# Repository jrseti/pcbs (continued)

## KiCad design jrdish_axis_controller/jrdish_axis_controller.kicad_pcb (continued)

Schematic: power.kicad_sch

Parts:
C46: 47uF; C1206; LCSC Part C403725
C47: 100nF; C0603; LCSC Part C14663
C48: 100nF; C_0402; Voltage Rated 50V; Tolerance ±10%; Part CL05B104KB54PNC; LCSC C307331
C49, C50: 10uF; C_0805; Voltage Rated 50V; Tolerance ±10%; Part GRM21BR61H106KE43L; LCSC C440198
C51: 100nF; C_0603; Voltage Rated 50V; Tolerance ±10%; Part CC0603KRX7R9BB104; LCSC C14663
C52: 22pF; C_0603; Voltage Rated 50V; Tolerance ±5%; Part CL10C220JB8NNNC; LCSC C1653
C53: 22uF; C_0805; Voltage Rated 25V; Tolerance ±20%; Part CL21A226MAQNNNE; LCSC C45783
C54: 1uF; C_0402; Voltage Rated 25V; Tolerance ±10%; Part CL05A105KA5NQNC; LCSC C52923
DC1: DC-005-2.5A-2.0; CONN-TH_DC-005-2.5A-2.0; LCSC Part C319099
F1: 1812L110/48QR; F1812; MPN 1812L110/48QR; LCSC Part C19723490
L11: 3.3uH; IND-SMD_L3.0-W3.0-1; LCSC Part C7427089
Q1, Q4: AO3407A; SOT-23-3_L2.9-W1.6-P1.90-LS2.8-BR; LCSC Part C15155
R20: 10kΩ; R_0603; Overload Voltage (Max) 75V; Tolerance ±1%; Part 0603WAF1002T5E; LCSC C22356465
R21: 976kΩ; R_0805_2012Metric; LCSC C865713
R22: 100kΩ; R_0603; Overload Voltage (Max) 75V; Tolerance ±1%; Part 0603WAF1003T5E; LCSC C25803
R23: 220kΩ; R_0603; Overload Voltage (Max) 75V; Tolerance ±1%; Part 0603WAF2203T5E; LCSC C22961
SW2: SS-12F49-G050; SW-TH_SS-12F45-GXXX; LCSC Part C2876010
TP1, TP2, TP3: RH-5016; TESTPOINT-SMD_L3.0-W2.0; MPN RH-5016; LCSC Part C5199799
U4: MP2322GQH-Z; QFN-8_L2.0-W1.5-P0.50-BL; LCSC Part C3726283

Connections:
12V: C49.1, C50.1, C51.1, Q1.3 (D), TP2.1 (1_1), U4.2 (IN), U4.3 (EN); also elsewhere on the board
/Power/12V_IN: DC1.1, F1.1, TP1.1 (1_1)
/Power/12V_IN_FUSED: C46.1, C47.1, F1.2, Q4.3 (D)
GND: C46.2, C47.2, C49.2, C50.2, C51.2, C53.2, C54.2, DC1.2, DC1.3, Q4.1 (G), R23.2, SW2.3, U4.1 (GND); also elsewhere on the board
unnamed: Q1.1 (G), SW2.2
unnamed: Q1.2 (S), Q4.2 (S), R20.1
unnamed: R20.2, SW2.1
unnamed: C48.2, U4.7 (BST)
unnamed: C52.2, R21.2, R23.1, U4.5 (FB)
unnamed: R22.1, U4.6 (PG)
unnamed: C48.1, L11.1, U4.8 (SW)
unnamed: C54.1, R22.2, U4.4 (VCC)

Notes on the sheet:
Off
12V DC input fused to 1.1A max
12V to 3V3 Buck
Q4 protects against reverse polarity. SW2 controls the gate of Q1, turning current on/off. The MOSFET is P-Channel.
12V_IN_FUSED is the input, 12V is the output (load)
Notes:
gate
0.1%
1.1A Fuse 48VDC
50V
From MP2322 Datasheet:
Reverse Voltage Protection P-Channel MOSFET
25V
Circuit to convert 12V DC to 3V3 DC 12V is reverse polatiry and over voltage protected MP2322 used to convert 12V to 3V3 DC 12V DC out will draw max 600mA 3V3 DC out will draw max 400mA Buck modeled after John Teel's YouTube video: https://www.youtube.com/watch?v=rLHW4gU6idU and referencing the MP2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
Power Flags

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
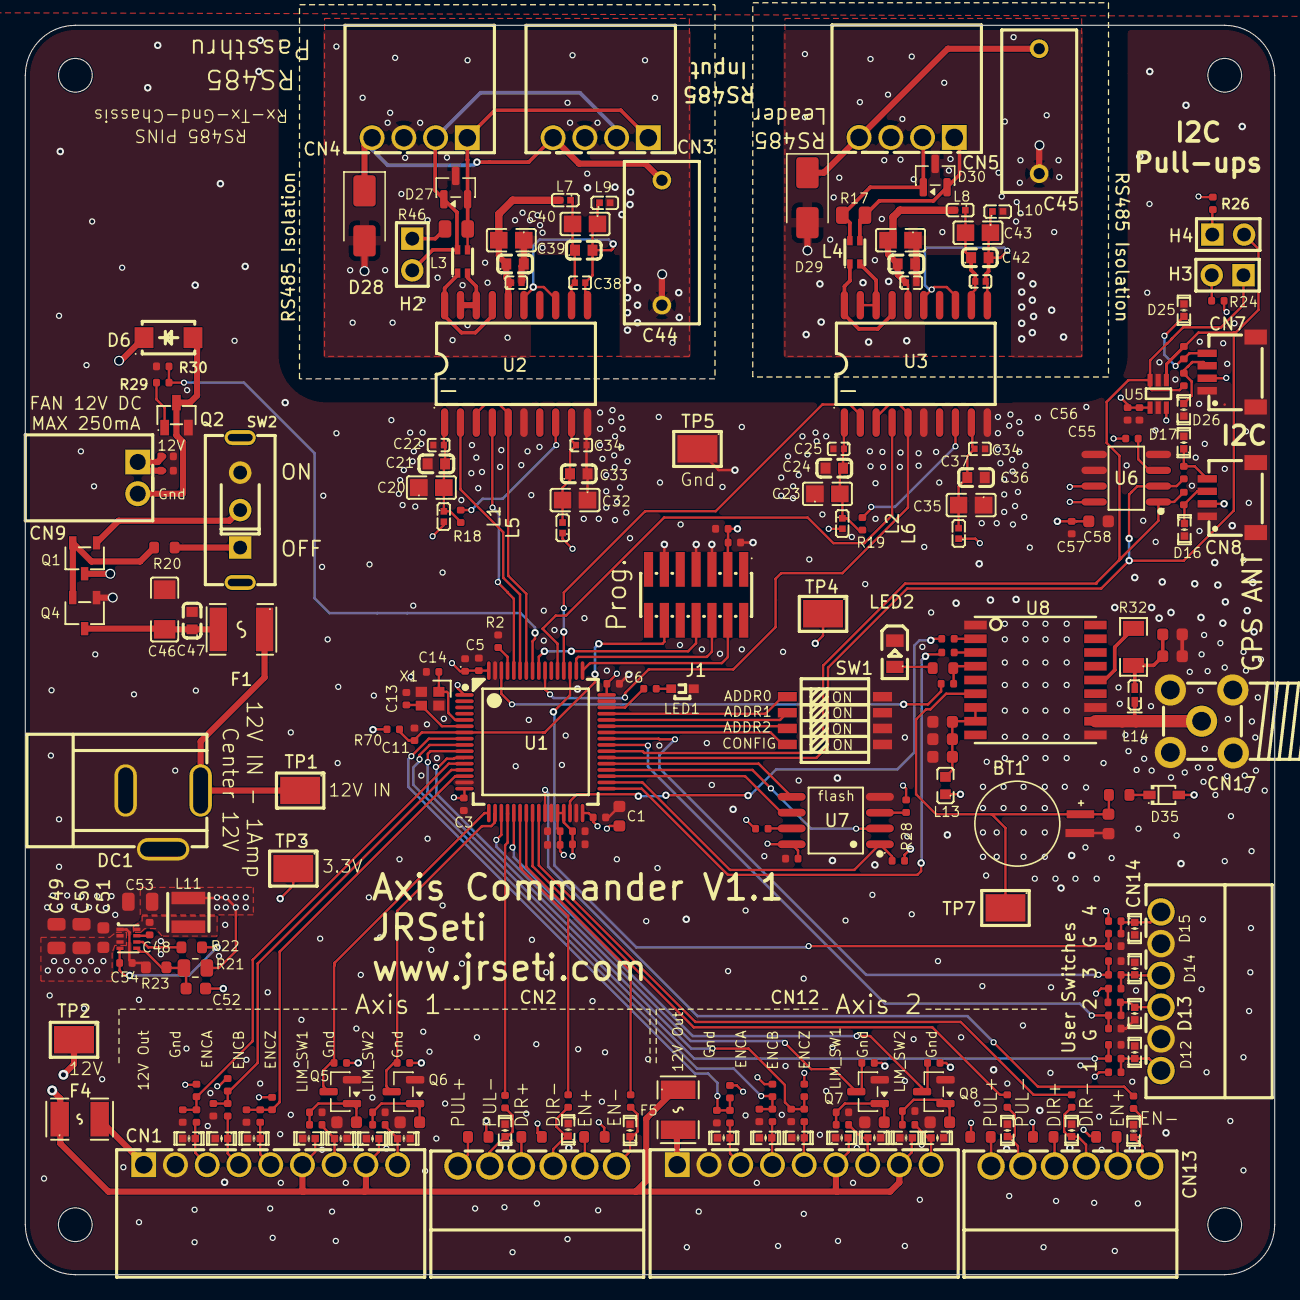
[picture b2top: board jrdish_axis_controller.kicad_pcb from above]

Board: 4 copper layers, 100.0 x 100.0 mm, 248 parts (0 on the bottom side), 140 nets.

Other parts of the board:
C12#2: 10nF; C_0603
M1, M1#2, M1#3, M1#4: MountingHole_2.7mm_M2.5_ISO14580

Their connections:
GND: C12#2.2; also elsewhere on the board

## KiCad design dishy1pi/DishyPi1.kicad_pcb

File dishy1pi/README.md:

# Dishy1Pi Hardware

The hardware part of the Dishy1Pi project is a Raspberry Pi Hat board which interfaces the Raspberry Pi GPIO pins with the satellite dish motor controllers, encoders, and various sensors. An important aspect of this board is that the Raspberry Pi is optically isolated from the hardware connected to the satellite dish.

Although this project is tailored to controlling a satellite dish, it can also be used for controlling other motor control systems that require isolation and encoder feedback.

## Parts Library

The PCB will be assembled by JCLPCB. The project will require parts number identification to be compatible with LCSC part numbers. See [Library README](libs/README.md)

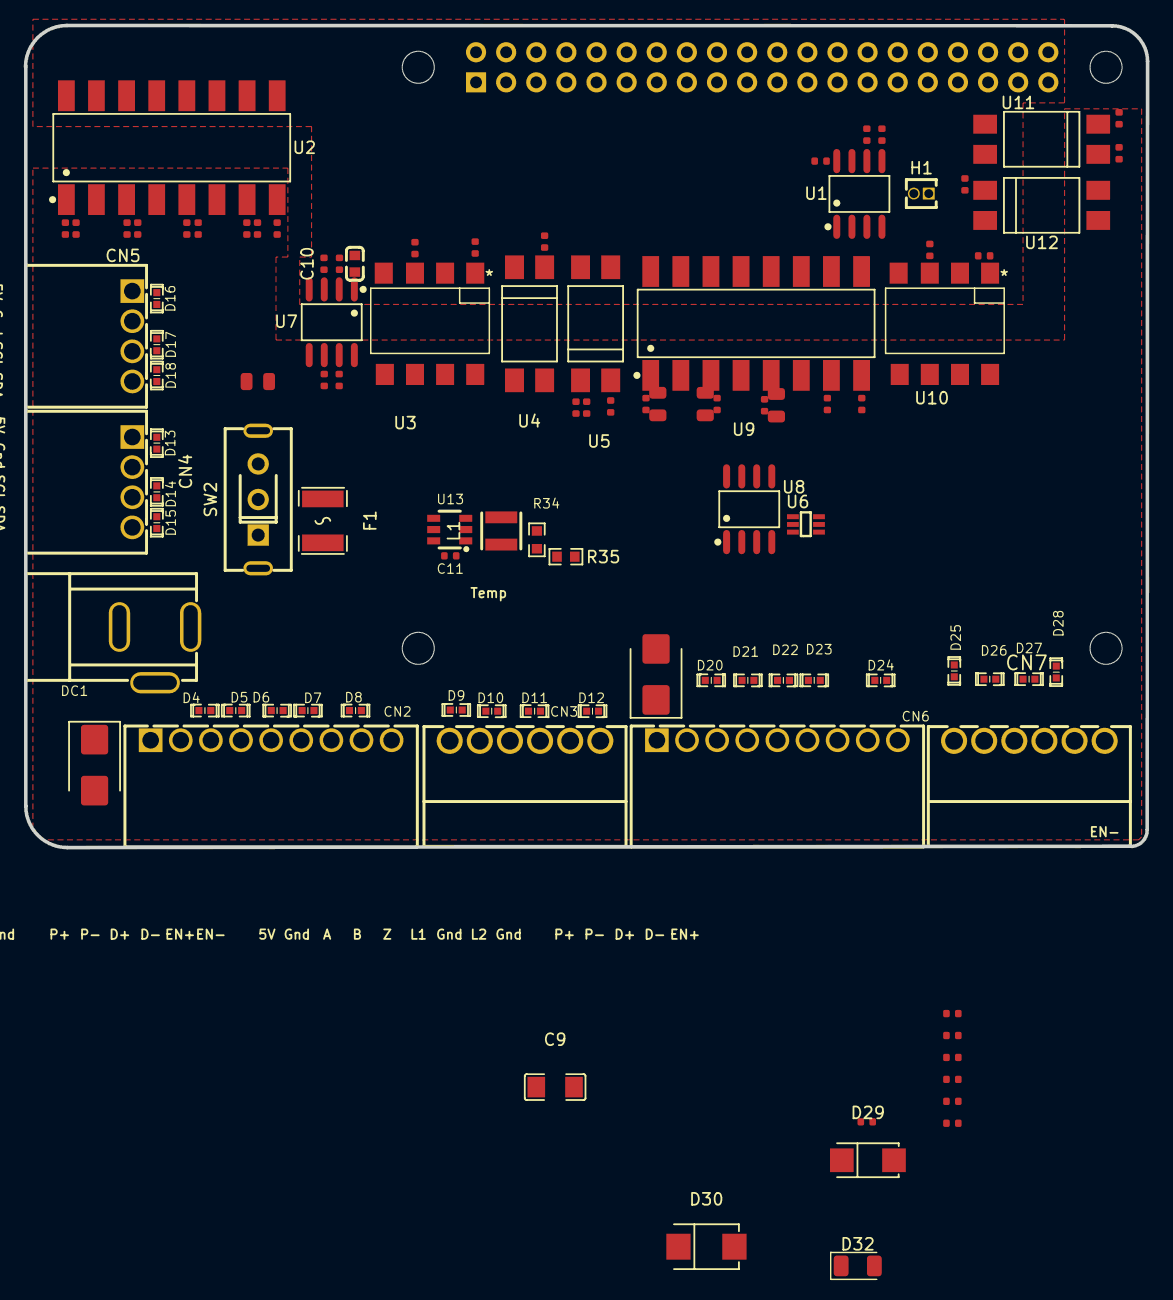
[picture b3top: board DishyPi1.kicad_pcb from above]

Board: 4 copper layers, 94.6 x 69.3 mm, 106 parts (1 on the bottom side), 67 nets, no tracks yet.

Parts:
C3, C5, C6, C7, C8, C11: 100nF; C_0402
C4: 100pF; C_0402
C9: 47uF; C1206
C10: 100nF; C0603
C12, C13, C14: 10uF; C_0805
C15: 100nF; C_0805
CN2, CN6: KF2EDGR-2.54-9P; CONN-TH_9P-P2.54_KF2EDGR-2.54-9P
CN3, CN7: KF2EDGR-2.54-6P; CONN-TH_KF2EDGR-2.54-6P
CN4, CN5: KF2EDGR-2.54-4P; CONN-TH_4P-P2.54_KF2EDGR-2.54-4P
D4, D5, D6, D7, D8, D9, D10, D11, D12, D13, D14, D15, D16, D17, D18, D20, D21, D22, D23, D24, D25, D26, D27, D28: TPESD0402G05V; D0402-BI
D29: SS34; SMA_L4.3-W2.6-LS5.2-RD
D30: SMBJ18A_C78412; SMB_L4.6-W3.6-LS5.3-RD
D32: LED; LED_1206_3216Metric
D33, D34: SMBJ16A; D_SMB
DC1: DC-005-2.5A-2.0; CONN-TH_DC-005-2.5A-2.0
F1: 1812L110/33MR; F1812
H1: 1.27MM/1*2P; HDR-TH_2P-P1.27-V-M
J1: Conn_02x20_Odd_Even; PinSocket_2x20_P2.54mm_Vertical
L1: 4.7uH; IND-SMD_L3.0-W3.0-1
MH1, MH2, MH3, MH4: MountingHole_2.7mm_M2.5
R2, R3: 3.9kΩ; R_0402
R4, R6, R8, R12, R13, R14, R21, R23, R25, R29, R30, R31: 1kΩ; R_0402
R5, R7, R9, R22, R24, R26: 10kΩ; R_0402
R10, R27: 220Ω; R_0402
R11, R16, R28, R33: 22kΩ; R_0402
R15, R32: 470Ω; R_0402
R17, R18, R19, R20: 4.7kΩ; R_0402
R34: 54.9k; R0603
R35: 10k; R0603
R36: 2.2kΩ; R_0402
SW2: SS-12F49-G050; SW-TH_SS-12F45-GXXX
U1: CAT24C256WI-GT3; SOIC-8_L4.9-W3.9-P1.27-LS6.0-BL
U2, U9: LTV-847S; SMD-16_L20.0-W6.5-P2.54-LS10.2-BL
U3, U10: LTV-827S-TA1; LTV827S-TA1
U4, U5, U11, U12: LTV-817S-TA1; LTV817S
U6: LTC4311ISC6#TRPBF; SC-70-6_L2.2-W1.3-P0.65-LS2.2-BL
U7: ISO1540DR; SOIC-8_L4.9-W3.9-P1.27-LS6.0-BL
U8: LM75BIMX-5/NOPB; SOIC-8_L4.9-W3.9-P1.27-LS6.0-BL
U13: TPS561201DDCR; SOT-23-6_L2.9-W1.6-P0.95-LS2.8-BR

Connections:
12V_PROT: C9.1, C10.1, C14.1, C15.1, CN2.1, CN6.1, D29.1 (K), D30.1 (K), D33.1, D34.1, U13.3 (VIN), U13.5 (EN)
+3.3V: C3.1, C6.1, H1.1, J1.1, J1.17, R2.1, R3.1, R17.1, R18.1, U1.8 (VCC), U7.1 (VCC1)
+5V: C5.1, C7.1, C8.1, C12.1, C13.1, CN3.1, CN3.3, CN3.5, CN4.1, CN5.1, CN7.1, CN7.3, CN7.5, D9.1 (K), D13.1 (K), D16.2 (A), D25.1 (K), D32.2 (A), L1.2, R4.1, R5.1, R6.1, R7.1, R8.1, R9.1, R10.1, R15.1, R16.2, R19.1, R20.1, R21.1, R22.1, R23.1, R24.1, R25.1, R26.1, R27.1, R28.2, R32.1, R33.2, R34.2, U6.1 (VCC), U6.3 (ENABLE), U7.8 (VCC2), U8.7 (A0), U8.8 (+VS)
/12v_in/12V_IN: DC1.1, SW2.1
/12v_in/VBST-SW-L1: C11.2, L1.1, U13.2 (SW)
/I2C/SCL: CN4.3, CN5.3, D14.1 (K), D17.2 (A), R20.2, U6.4 (BUS2), U7.6 (SCL2), U8.2 (SCL)
/I2C/SDA: CN4.4, CN5.4, D15.1 (K), D18.2 (A), R19.2, U6.6 (BUS1), U7.7 (SDA2), U8.1 (SDA)
/ID_SCL: J1.28, R2.2, U1.6 (SCL)
/ID_SDA: J1.27, R3.2, U1.5 (SDA)
/IO/DIR-: CN3.4, D11.1 (K), U3.8
/IO/ENC_A: CN2.3, D4.1 (K), R9.2, U2.2 (CAT1)
/IO/ENC_B: CN2.4, D5.1 (K), R7.2, U2.4 (CAT2)
/IO/ENC_Z: CN2.5, D6.1 (K), R5.2, U2.6 (CAT3)
/IO/LIM_1: CN2.6, D7.1 (K), R11.1, U2.8 (CAT4)
/IO/LIM_2: CN2.8, D8.1 (K), R16.1, U5.2
/IO/MF-: CN3.6, D12.1 (K), U4.4
/IO/PUL-: CN3.2, D10.1 (K), U3.6
/io2/DIR-: CN7.4, D27.1 (K), U10.6
/io2/ENC_A: CN6.3, D20.1 (K), R26.2, U9.2 (CAT1)
/io2/ENC_B: CN6.4, D21.1 (K), R24.2, U9.4 (CAT2)
/io2/ENC_Z: CN6.5, D22.1 (K), R22.2, U9.6 (CAT3)
/io2/LIM_1: CN6.6, D23.1 (K), R28.1, U9.8 (CAT4)
/io2/LIM_2: CN6.8, D24.1 (K), R33.1, U12.2
/io2/MF-: CN7.6, D28.1 (K), U11.4
/io2/PUL-: CN7.2, D26.1 (K), U10.8
A_DIR/19: J1.35, R30.1
A_ENC_A/5: J1.29, U9.16 (COL1)
A_ENC_B/6: J1.31, U9.14 (COL2)
A_ENC_Z/26: J1.37, U9.12 (COL3)
A_LIM_1/12: J1.32, U9.10 (COL4)
A_LIM_2/21: J1.40, U12.4
A_MF/20: J1.38, R31.1
A_PUL/13: J1.33, R29.1
E_DIR/23: J1.16, R12.1
E_ENC_A/17: J1.11, U2.16 (COL1)
E_ENC_B/22: J1.13, U2.14 (COL2)
E_ENC_Z/27: J1.15, U2.12 (COL3)
E_LIM_1/25: J1.22, U2.10 (COL4)
E_LIM_2/16: J1.36, U5.4
E_MF/24: J1.18, R14.1
E_PUL/18: J1.12, R13.1
GNDIO: C4.2, C5.2, C7.2, C8.2, C9.2, C10.2, C12.2, C13.2, C14.2, C15.2, CN2.2, CN2.7, CN2.9, CN4.2, CN5.2, CN6.2, CN6.7, CN6.9, D4.2 (A), D5.2 (A), D6.2 (A), D7.2 (A), D8.2 (A), D9.2 (A), D10.2 (A), D11.2 (A), D12.2 (A), D13.2 (A), D14.2 (A), D15.2 (A), D16.1 (K), D17.1 (K), D18.1 (K), D20.2 (A), D21.2 (A), D22.2 (A), D23.2 (A), D24.2 (A), D25.2 (A), D26.2 (A), D27.2 (A), D28.2 (A), D30.2 (A), D33.2, D34.2, DC1.2, DC1.3, R11.2, R35.2, R36.2, U3.5, U3.7, U4.3, U6.2 (GND), U6.5 (GND), U7.5 (GND2), U8.4 (GND), U8.5 (A2), U8.6 (A1), U10.5, U10.7, U11.3, U13.1 (GND)
GNDPI: C3.2, C6.2, J1.6, J1.9, J1.14, J1.20, J1.25, J1.30, J1.34, J1.39, U1.1 (A0), U1.2 (A1), U1.3 (A2), U1.4 (VSS), U2.9 (EM4), U2.11 (EM3), U2.13 (EM2), U2.15 (EM1), U3.2, U3.4, U4.2, U5.3, U7.4 (GND1), U9.9 (EM4), U9.11 (EM3), U9.13 (EM2), U9.15 (EM1), U10.2, U10.4, U11.2, U12.3
unnamed: D29.2 (A), F1.2
unnamed: D32.1 (K), R36.1
unnamed: F1.1, SW2.2
unnamed: R12.2, U3.1
unnamed: R13.2, U3.3
unnamed: R14.2, U4.1
unnamed: R15.2, U5.1
unnamed: R29.2, U10.1
unnamed: R30.2, U10.3
unnamed: R31.2, U11.1
unnamed: R32.2, U12.1
unnamed: H1.2, U1.7 (WP)
unnamed: R8.2, U2.1 (AN1)
unnamed: R6.2, U2.3 (AN2)
unnamed: R4.2, U2.5 (AN3)
unnamed: C4.1, R10.2, U2.7 (AN4)
unnamed: R25.2, U9.1 (AN1)
unnamed: R23.2, U9.3 (AN2)
unnamed: R21.2, U9.5 (AN3)
unnamed: R27.2, U9.7 (AN4)
unnamed: C11.1, U13.6 (VBST)
unnamed: R34.1, R35.1, U13.4 (VFB)
PI_SCL: J1.5, R17.2, U7.3 (SCL1)
PI_SDA: J1.3, R18.2, U7.2 (SDA1)

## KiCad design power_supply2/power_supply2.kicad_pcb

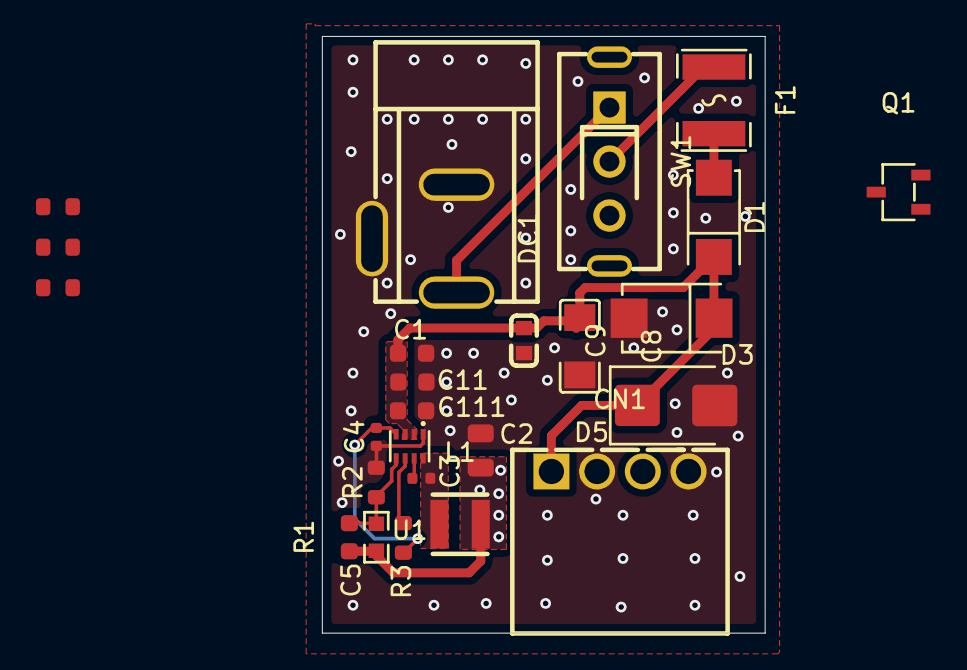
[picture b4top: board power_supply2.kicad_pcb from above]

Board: 4 copper layers, 24.6 x 33.1 mm, 25 parts (0 on the bottom side), 13 nets.

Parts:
C1: 100nF; C_0603
C2: 22uF; C_0805
C3: 22pF; C_0402
C4: 1uF; C_0402
C5: 22pF; C_0603
C8: 47uF; C1206
C9: 100nF; C0603
C11, C111: 10uF; C_0603
CN1: KF2EDGR-2.54-4P; CONN-TH_4P-P2.54_KF2EDGR-2.54-4P
D1: SS34; SMA_L4.3-W2.6-LS5.2-RD
D3: SMBJ18A; SMB_L4.6-W3.6-LS5.3-RD
D5: SMBJ16A; D_SMB
DC1: DC-005-2.5A-2.0; CONN-TH_DC-005-2.5A-2.0
F1: 1812L110/33MR; F1812
L1: 4.7uH; IND-SMD_L3.0-W3.0-1
Q1: AO3407A; SOT-23-3_L2.9-W1.6-P1.90-LS2.8-BR
R1: 1621Ω; R0603
R2: 220kΩ; R_0603
R2#2: 220Ω; R_0603
R3: 200kΩ; R_0603
R3#2: 100kΩ; R_0603
R4: 10kΩ; R_0603
SW1: SS-12F49-G050; SW-TH_SS-12F45-GXXX
U1: MP2322GQH-Z; QFN-8_L2.0-W1.5-P0.50-BL

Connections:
/5V_OUT: C2.1, C5.1, CN1.3, L1.2, R1.1
/12V_IN: DC1.1, F1.1
/12V_IN_FUSED: C8.1, C9.1, F1.2, Q1.3 (D), R4.1
/12V_OUT: C1.1, C11.1, C111.1, CN1.1, Q1.2 (S), U1.2 (IN), U1.3 (EN)
/12V_PROT: D1.1 (K), D3.1 (K), D5.1
GND: C1.2, C2.2, C4.2, C8.2, C9.2, C11.2, C111.2, CN1.2, CN1.4, D3.2 (A), D5.2, DC1.2, DC1.3, R2.2, R2#2.2, SW1.3, U1.1 (GND)
unnamed: Q1.1 (G), SW1.2
unnamed: R4.2, SW1.1
unnamed: C3.1, U1.7 (BST)
unnamed: C5.2, R1.2, R2.1, R2#2.1, U1.5 (FB)
unnamed: R3.1, R3#2.1, U1.6 (PG)
unnamed: C3.2, L1.1, U1.8 (SW)
unnamed: C4.1, R3.2, R3#2.2, U1.4 (VCC)

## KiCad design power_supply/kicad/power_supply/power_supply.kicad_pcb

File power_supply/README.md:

# Power Supply

This is a simple PCB to test creating several voltages that are used on the Dishy1Pi PCB. Once this cirction is tested as working, the relevant schematic parts will be moved over to the DishyPi1 schematic. The voltages needed are:
- 12V to power each of the 2 encoders. This voltage is supplied from an external power supply and protected by a PTC fuse on the Dishy1Pi PCB. Also reverse polatiry protected.
- 5V to power the logic circuity on the Dishy1Pi PCB. This voltage is generated on this power supply PCB from the 12-24V input voltage using a buck converter.

I need to learn how to design a power supply for a PCB board and get some experience with power supply design.

Project Goals:
- Design a power supply PCB that can take an input voltage range of 12-24VDC
- Output a stable 5VDC at up to 1A
Output clean 12V for each of the 2 encoders
- Create a schematic and PCB layout for the power supply that can be manufactured by JLCPCB.
- Get a board manufactureed and assembled by JLCPCB and test it, verify it works.
- Move the design of the power circuit to the dishy1pi project.

KiCad will be used for this project.

Used TI's WEBENCH Power Designer to design the power supply around the TPS561201DDCR buck converter IC. Link: https://webench.ti.com/power-designer/

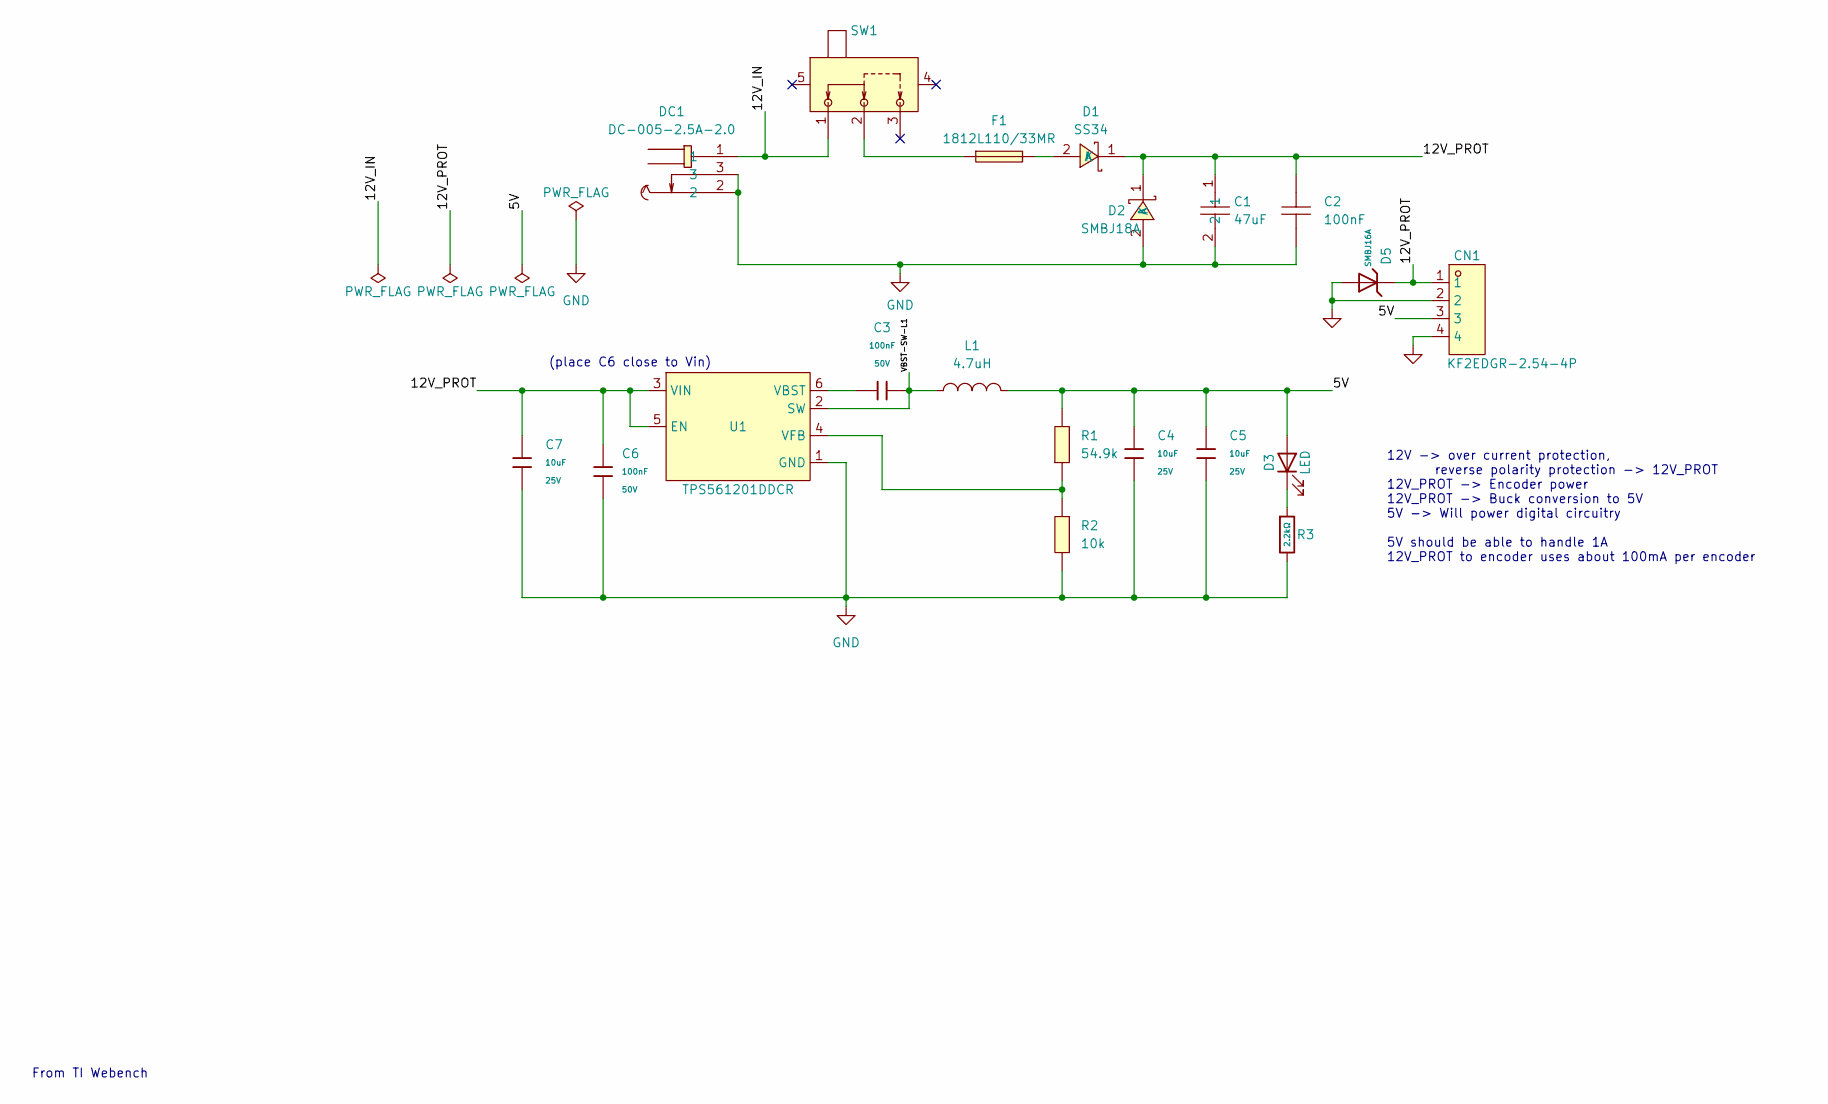
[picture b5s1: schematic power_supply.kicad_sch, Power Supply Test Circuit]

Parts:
C1: 47uF; C1206; LCSC Part C403725
C2: 100nF; C0603; LCSC Part C14663
C3: 100nF; C_0402; Voltage Rated 50V; Tolerance ±10%; Part CL05B104KB54PNC; LCSC C307331
C4, C5, C7: 10uF; C_0805; Voltage Rated 25V; Tolerance ±10%; Part CL21A106KAYNNNE; LCSC C15850
C6: 100nF; C_0805; Voltage Rated 50V; Tolerance ±10%; Part CC0805KRX7R9BB104; LCSC C49678
CN1: KF2EDGR-2.54-4P; CONN-TH_4P-P2.54_KF2EDGR-2.54-4P; LCSC Part C577596
D1: SS34; SMA_L4.3-W2.6-LS5.2-RD; LCSC Part C8678
D2: SMBJ18A; SMB_L4.6-W3.6-LS5.3-RD; LCSC Part C2965323
D3: LED; LED_1206_3216Metric; LCSC Part C5264252
D5: SMBJ16A; D_SMB; Part SMBJ16A; LCSC C19077571
DC1: DC-005-2.5A-2.0; CONN-TH_DC-005-2.5A-2.0; LCSC Part C319099
F1: 1812L110/33MR; F1812; LCSC Part C142747
L1: 4.7uH; IND-SMD_L3.0-W3.0-1; LCSC Part C7427089
R1: 54.9k; R0603; LCSC Part C23077
R2: 10k; R0603; LCSC Part C25804
R3: 2.2kΩ; R_0402; Overload Voltage (Max) 50V; Tolerance ±1%; Part 0402WGF2201TCE; LCSC C25879
SW1: SS-12F49-G050; SW-TH_SS-12F45-GXXX; LCSC Part C2876010
U1: TPS561201DDCR; SOT-23-6_L2.9-W1.6-P0.95-LS2.8-BR; LCSC Part C220433

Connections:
/5V: C4.1, C5.1, CN1.3, D3.2 (A), L1.2, R1.2
/12V_IN: DC1.1, SW1.1
/12V_PROT: C1.1, C2.1, C6.1, C7.1, CN1.1, D1.1 (K), D2.1 (K), D5.1, U1.3 (VIN), U1.5 (EN)
/VBST-SW-L1: C3.2, L1.1, U1.2 (SW)
GND: C1.2, C2.2, C4.2, C5.2, C6.2, C7.2, CN1.2, CN1.4, D2.2 (A), D5.2, DC1.2, DC1.3, R2.2, R3.2, U1.1 (GND)
unnamed: D1.2 (A), F1.2
unnamed: D3.1 (K), R3.1
unnamed: F1.1, SW1.2
unnamed: C3.1, U1.6 (VBST)
unnamed: R1.1, R2.1, U1.4 (VFB)

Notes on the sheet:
From TI Webench
(place C6 close to Vin)
12V -> over current protection, reverse polarity protection -> 12V_PROT 12V_PROT -> Encoder power 12V_PROT -> Buck conversion to 5V 5V -> Will power digital circuitry 5V should be able to handle 1A 12V_PROT to encoder uses about 100mA per encoder

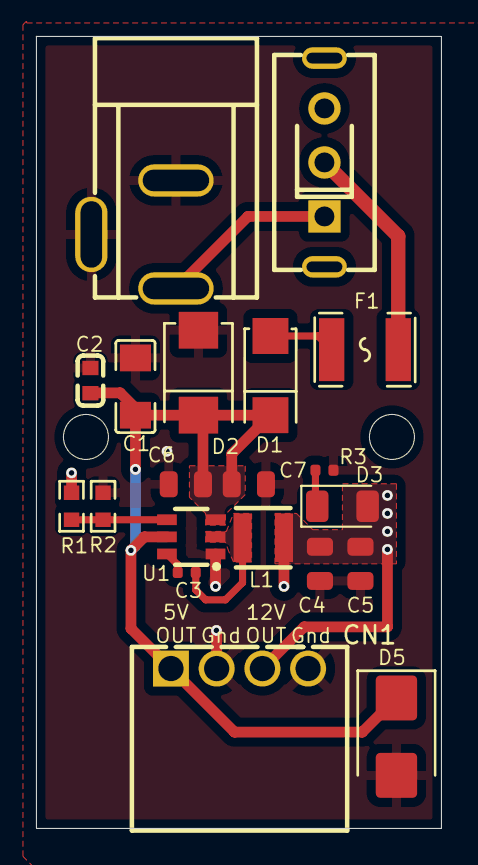
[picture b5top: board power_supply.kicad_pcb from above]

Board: 4 copper layers, 22.5 x 44.0 mm, 20 parts (0 on the bottom side), 10 nets.

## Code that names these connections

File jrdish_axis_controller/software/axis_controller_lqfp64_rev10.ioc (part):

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Mcu.Name=STM32G474R(B-C-E)Tx
Mcu.Package=LQFP64
Mcu.UserName=STM32G474RETx
PA0.GPIOParameters=GPIO_Label
PA0.GPIO_Label=ENC1_A
PA0.Signal=S_TIM2_CH1
PA1.GPIOParameters=GPIO_Label
PA1.GPIO_Label=ENC1_B
PA1.Signal=S_TIM2_CH2
PA10.GPIOParameters=GPIO_PuPd,GPIO_Label
PA10.GPIO_Label=ADDR1
PA10.GPIO_PuPd=GPIO_PULLUP
PA10.Signal=GPIO_Input
PA11.GPIOParameters=GPIO_PuPd,GPIO_Label
PA11.GPIO_Label=ADDR0
PA11.GPIO_PuPd=GPIO_PULLUP
PA11.Signal=GPIO_Input
PA12.GPIOParameters=GPIO_Label
PA12.GPIO_Label=STATUS_LED
PA12.Signal=GPIO_Output
PA13.Mode=Trace_Asynchronous_SW
PA13.Signal=SYS_JTMS-SWDIO
PA14.Mode=Trace_Asynchronous_SW
PA14.Signal=SYS_JTCK-SWCLK
PA15.GPIOParameters=GPIO_PuPd,GPIO_Label
PA15.GPIO_Label=USER_SW_4
PA15.GPIO_PuPd=GPIO_PULLUP
PA15.Signal=GPIO_Input
PA2.GPIOParameters=GPIO_PuPd,GPIO_Label
PA2.GPIO_Label=ENC1_Z
PA2.GPIO_PuPd=GPIO_PULLUP
PA2.Signal=GPXTI2
PA3.GPIOParameters=GPIO_PuPd,GPIO_Label
PA3.GPIO_Label=LIMIT1_SW1
PA3.GPIO_PuPd=GPIO_PULLUP
PA3.Signal=GPIO_Input
PA4.GPIOParameters=GPIO_PuPd,GPIO_Label
PA4.GPIO_Label=LIMIT1_SW2
PA4.GPIO_PuPd=GPIO_PULLUP
PA4.Signal=GPIO_Input
PA5.GPIOParameters=GPIO_PuPd,GPIO_Label
PA5.GPIO_Label=LIMIT2_SW1
PA5.GPIO_PuPd=GPIO_PULLUP
PA5.Signal=GPIO_Input
PA6.GPIOParameters=GPIO_Label
PA6.GPIO_Label=PUL1
PA6.Signal=S_TIM16_CH1
PA7.GPIOParameters=GPIO_PuPd,GPIO_Label
PA7.GPIO_Label=LIMIT2_SW2
PA7.GPIO_PuPd=GPIO_PULLUP
PA7.Signal=GPIO_Input
PA8.GPIOParameters=GPIO_PuPd,GPIO_Label
PA8.GPIO_Label=CONFIG_SW
PA8.GPIO_PuPd=GPIO_PULLUP
PA8.Signal=GPIO_Input
PA9.GPIOParameters=GPIO_PuPd,GPIO_Label
PA9.GPIO_Label=ADDR2
PA9.GPIO_PuPd=GPIO_PULLUP
PA9.Signal=GPIO_Input
PB0.GPIOParameters=GPIO_Label
PB0.GPIO_Label=PUL2
PB0.Signal=S_TIM3_CH3
PB1.GPIOParameters=GPIO_Label
PB1.GPIO_Label=DIR2
PB1.Signal=GPIO_Output
PB10.GPIOParameters=GPIO_Label
PB10.GPIO_Label=RS232_RX
PB10.Mode=Asynchronous
PB10.Signal=LPUART1_RX
PB11.GPIOParameters=GPIO_Label
PB11.GPIO_Label=RS232_TX
PB11.Mode=Asynchronous
PB11.Signal=LPUART1_TX
PB12.GPIOParameters=GPIO_Speed,GPIO_Label,GPIO_ModeDefaultOutputPP
PB12.GPIO_Label=FLASH_CS
PB12.GPIO_ModeDefaultOutputPP=GPIO_MODE_OUTPUT_PP
PB12.GPIO_Speed=GPIO_SPEED_FREQ_HIGH
PB12.Signal=GPIO_Output
PB13.Mode=Full_Duplex_Master
PB13.Signal=SPI2_SCK
PB14.Mode=Full_Duplex_Master
PB14.Signal=SPI2_MISO
PB15.Mode=Full_Duplex_Master
PB15.Signal=SPI2_MOSI
PB2.GPIOParameters=GPIO_Label
PB2.GPIO_Label=ENABLE2
PB2.Signal=GPIO_Output
PB3.Mode=Trace_Asynchronous_SW
PB3.Signal=SYS_JTDO-SWO
PB4.GPIOParameters=GPIO_Label
PB4.GPIO_Label=FAN
PB4.Signal=GPIO_Output
PB5.GPIOParameters=GPIO_Label
PB5.GPIO_Label=RS485_1_DE
PB5.Signal=GPIO_Output
PB6.GPIOParameters=GPIO_Label
PB6.GPIO_Label=RS485_1_TX
PB6.Mode=Asynchronous
PB6.Signal=USART1_TX
PB7.GPIOParameters=GPIO_Label
PB7.GPIO_Label=RS485_1_RX
PB7.Mode=Asynchronous
PB7.Signal=USART1_RX
PB9.GPIOParameters=GPIO_Label
PB9.GPIO_Label=GPS_1PPS
PB9.Signal=S_TIM17_CH1
PC0.GPIOParameters=GPIO_Label
PC0.GPIO_Label=ENC2_A
PC0.Signal=S_TIM1_CH1
PC1.GPIOParameters=GPIO_Label
PC1.GPIO_Label=ENC2_B
PC1.Signal=S_TIM1_CH2
PC10.GPIOParameters=GPIO_Label
PC10.GPIO_Label=RS485_2_TX
PC10.Mode=Asynchronous
PC10.Signal=USART3_TX
PC11.GPIOParameters=GPIO_Label
PC11.GPIO_Label=RS485_2_RX
PC11.Mode=Asynchronous
PC11.Signal=USART3_RX
PC2.GPIOParameters=GPIO_PuPd,GPIO_Label
PC2.GPIO_Label=USER_SW_1
PC2.GPIO_PuPd=GPIO_PULLUP
PC2.Signal=GPIO_Input
PC3.GPIOParameters=GPIO_PuPd,GPIO_Label
PC3.GPIO_Label=ENC2_Z
PC3.GPIO_PuPd=GPIO_PULLUP
PC3.Signal=GPXTI3
PC4.GPIOParameters=GPIO_Label
PC4.GPIO_Label=DIR1
PC4.Signal=GPIO_Output
PC5.GPIOParameters=GPIO_Label
PC5.GPIO_Label=ENABLE1
PC5.Signal=GPIO_Output
PC6.Mode=I2C
PC6.Signal=I2C4_SCL
PC7.Mode=I2C
PC7.Signal=I2C4_SDA
PC8.GPIOParameters=GPIO_PuPd,GPIO_Label
PC8.GPIO_Label=USER_SW_2
PC8.GPIO_PuPd=GPIO_PULLUP
PC8.Signal=GPIO_Input
PC9.GPIOParameters=GPIO_PuPd,GPIO_Label
PC9.GPIO_Label=USER_SW_3
PC9.GPIO_PuPd=GPIO_PULLUP
PC9.Signal=GPIO_Input
PD2.GPIOParameters=GPIO_Label
PD2.GPIO_Label=RS485_2_DE
PD2.Signal=GPIO_Output
PF0-OSC_IN.Mode=HSE-External-Oscillator
PF0-OSC_IN.Signal=RCC_OSC_IN
PF1-OSC_OUT.Mode=HSE-External-Oscillator
PF1-OSC_OUT.Signal=RCC_OSC_OUT
RCC.HSE_VALUE=16000000
RCC.SYSCLKFreq_VALUE=170000000
RCC.SYSCLKSource=RCC_SYSCLKSOURCE_PLLCLK
board=custom

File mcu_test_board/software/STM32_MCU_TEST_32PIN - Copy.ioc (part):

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Mcu.Name=STM32G431K(6-8-B)Tx
Mcu.Package=LQFP32
Mcu.UserName=STM32G431KBTx
PA0.GPIOParameters=GPIO_Label
PA0.GPIO_Label=ENC_A
PA0.Signal=S_TIM2_CH1
PA1.GPIOParameters=GPIO_Label
PA1.GPIO_Label=ENC_B
PA1.Signal=S_TIM2_CH2
PA10.GPIOParameters=GPIO_PuPd,GPIO_Label
PA10.GPIO_Label=ADDR1
PA10.GPIO_PuPd=GPIO_PULLUP
PA10.Signal=GPIO_Input
PA11.GPIOParameters=GPIO_PuPd,GPIO_Label
PA11.GPIO_Label=ADDR2
PA11.GPIO_PuPd=GPIO_PULLUP
PA11.Signal=GPIO_Input
PA12.GPIOParameters=GPIO_Label
PA12.GPIO_Label=STATUS_LED
PA12.Signal=GPIO_Output
PA13.Mode=Trace_Asynchronous_SW
PA13.Signal=SYS_JTMS-SWDIO
PA14.Mode=Trace_Asynchronous_SW
PA14.Signal=SYS_JTCK-SWCLK
PA2.GPIOParameters=GPIO_PuPd,GPIO_Label,GPIO_ModeDefaultEXTI
PA2.GPIO_Label=ECN_Z
PA2.GPIO_ModeDefaultEXTI=GPIO_MODE_IT_RISING
PA2.GPIO_PuPd=GPIO_PULLUP
PA2.Signal=GPXTI2
PA3.GPIOParameters=GPIO_PuPd,GPIO_Label
PA3.GPIO_Label=LIMIT_SW1
PA3.GPIO_PuPd=GPIO_PULLUP
PA3.Signal=GPIO_Input
PA4.GPIOParameters=GPIO_PuPd,GPIO_Label
PA4.GPIO_Label=LIMIT_SW2
PA4.GPIO_PuPd=GPIO_PULLUP
PA4.Signal=GPIO_Input
PA6.GPIOParameters=GPIO_Label
PA6.GPIO_Label=ENABLE
PA6.Signal=GPIO_Output
PA7.GPIOParameters=GPIO_Label
PA7.GPIO_Label=DIR
PA7.Signal=GPIO_Output
PA8.Mode=I2C
PA8.Signal=I2C3_SCL
PA9.GPIOParameters=GPIO_PuPd,GPIO_Label
PA9.GPIO_Label=ADDR0
PA9.GPIO_PuPd=GPIO_PULLUP
PA9.Signal=GPIO_Input
PB0.GPIOParameters=GPIO_Label
PB0.GPIO_Label=PUL
PB0.Signal=S_TIM3_CH3
PB3.Mode=Trace_Asynchronous_SW
PB3.Signal=SYS_JTDO-SWO
PB5.Mode=I2C
PB5.Signal=I2C3_SDA
PB6.Mode=Asynchronous
PB6.Signal=USART1_TX
PB7.Mode=Asynchronous
PB7.Signal=USART1_RX
PF0-OSC_IN.Mode=HSE-External-Oscillator
PF0-OSC_IN.Signal=RCC_OSC_IN
PF1-OSC_OUT.Mode=HSE-External-Oscillator
PF1-OSC_OUT.Signal=RCC_OSC_OUT
RCC.HSE_VALUE=8000000
RCC.SYSCLKFreq_VALUE=170000000
RCC.SYSCLKSource=RCC_SYSCLKSOURCE_PLLCLK
board=custom

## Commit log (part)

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2026-03-29 Added parts submodule
2026-03-29 Added README
2026-03-29 Removed parts
2026-03-29 Added first content
2026-03-29 Added content
2026-03-29 Added mcu_test_board
2026-03-29 Added MCU software
2026-03-30 Added requirements.txt for Python
2026-03-30 Added parts
2026-03-30 Added power_supply
2026-03-31 Updates, power_supply_2 added
2026-03-31 Added dishy1pi
2026-04-05 Latest FW testing
2026-04-05 Lastest FW update
2026-04-09 Added
2026-04-10 Building first version...
2026-04-12 Passes ERC
2026-04-13 PCB layout in progress
2026-04-15 Layout no ERC errors
2026-04-22 New 64pin version - 2 axes
2026-04-22 Added latest ioc
2026-04-23 Continuing layout
2026-04-29 RS485 isolated areas in place
2026-04-29 Near finished routing
2026-04-29 Layout complete
2026-04-30 Making refinements
2026-05-04 Limit switches with mosfets
2026-05-04 Removed RS232 chip, not 3.3V UART only
2026-05-05 Refinements...
2026-05-05 Minor adjustments
